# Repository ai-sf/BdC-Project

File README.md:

# Botta di Coulomb (BdC)

Quiz scientifico interattivo con scopi divulgativi, creato dall'Associazione Italiana Studenti di Fisica, Comitato Locale di Pavia. Realizzato in occasione della Notte Europea dei Ricercatori 2017 e riproposto in numerose altre occasioni.

Multi-player quiz game, designed for popularization activities: first developed for the European Researchers' Night 2017 by [AISF](http://ai-sf.it/) Pavia, and proposed in several other public or private events.

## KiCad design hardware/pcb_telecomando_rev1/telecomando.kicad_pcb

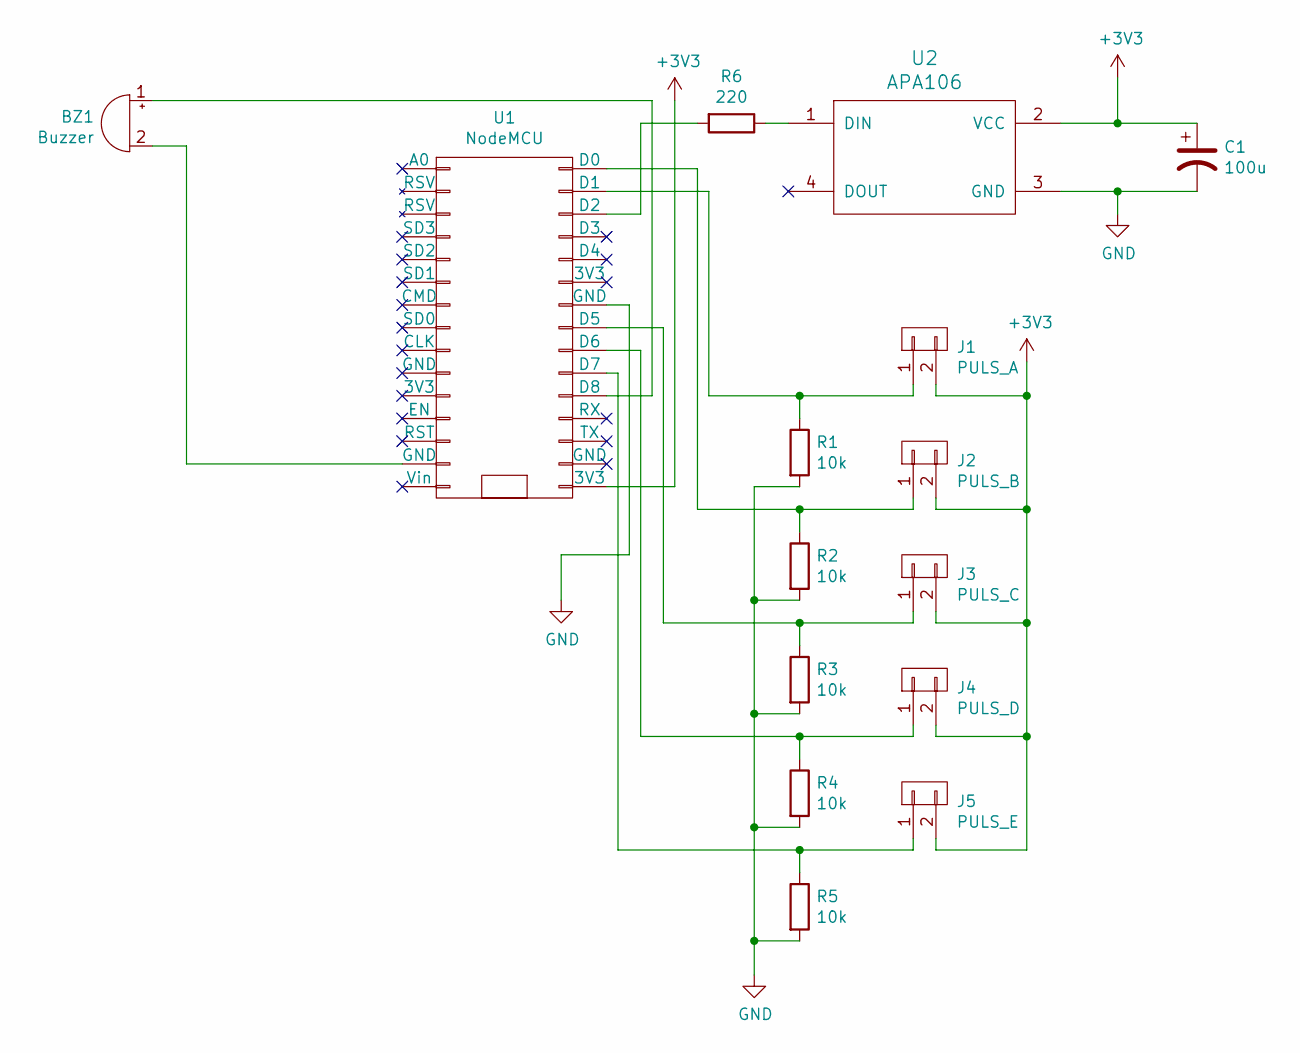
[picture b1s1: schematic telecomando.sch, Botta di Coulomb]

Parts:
BZ1: Buzzer; Buzzer_12x9.5RM7.6
C1: 100u; CP_Radial_D8.0mm_P2.50mm
J1: PULS_A; SW_PUSH-12mm
J2: PULS_B; SW_PUSH-12mm
J3: PULS_C; SW_PUSH-12mm
J4: PULS_D; SW_PUSH-12mm
J5: PULS_E; SW_PUSH-12mm
R1, R2, R3, R4, R5: 10k; Resistor_Horizontal_RM10mm
R6: 220; Resistor_Horizontal_RM10mm
U1: NodeMCU; NodeMCU_0.9
U2: APA106

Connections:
+3V3: C1.1, J1.2, J2.2, J3.2, J4.2, J5.2, U1.16 (3V3), U2.2 (VCC)
GND: C1.2, R1.2, R2.2, R3.2, R4.2, R5.2, U1.24 (GND), U2.3 (GND)
unnamed: BZ1.1 (-), U1.20 (D8)
unnamed: BZ1.2 (+), U1.14 (GND)
unnamed: J1.1, R1.1, U1.29 (D1)
unnamed: J2.1, R2.1, U1.30 (D0)
unnamed: J3.1, R3.1, U1.23 (D5)
unnamed: J4.1, R4.1, U1.22 (D6)
unnamed: J5.1, R5.1, U1.21 (D7)
unnamed: R6.1, U2.1 (DIN)
unnamed: R6.2, U1.28 (D2)

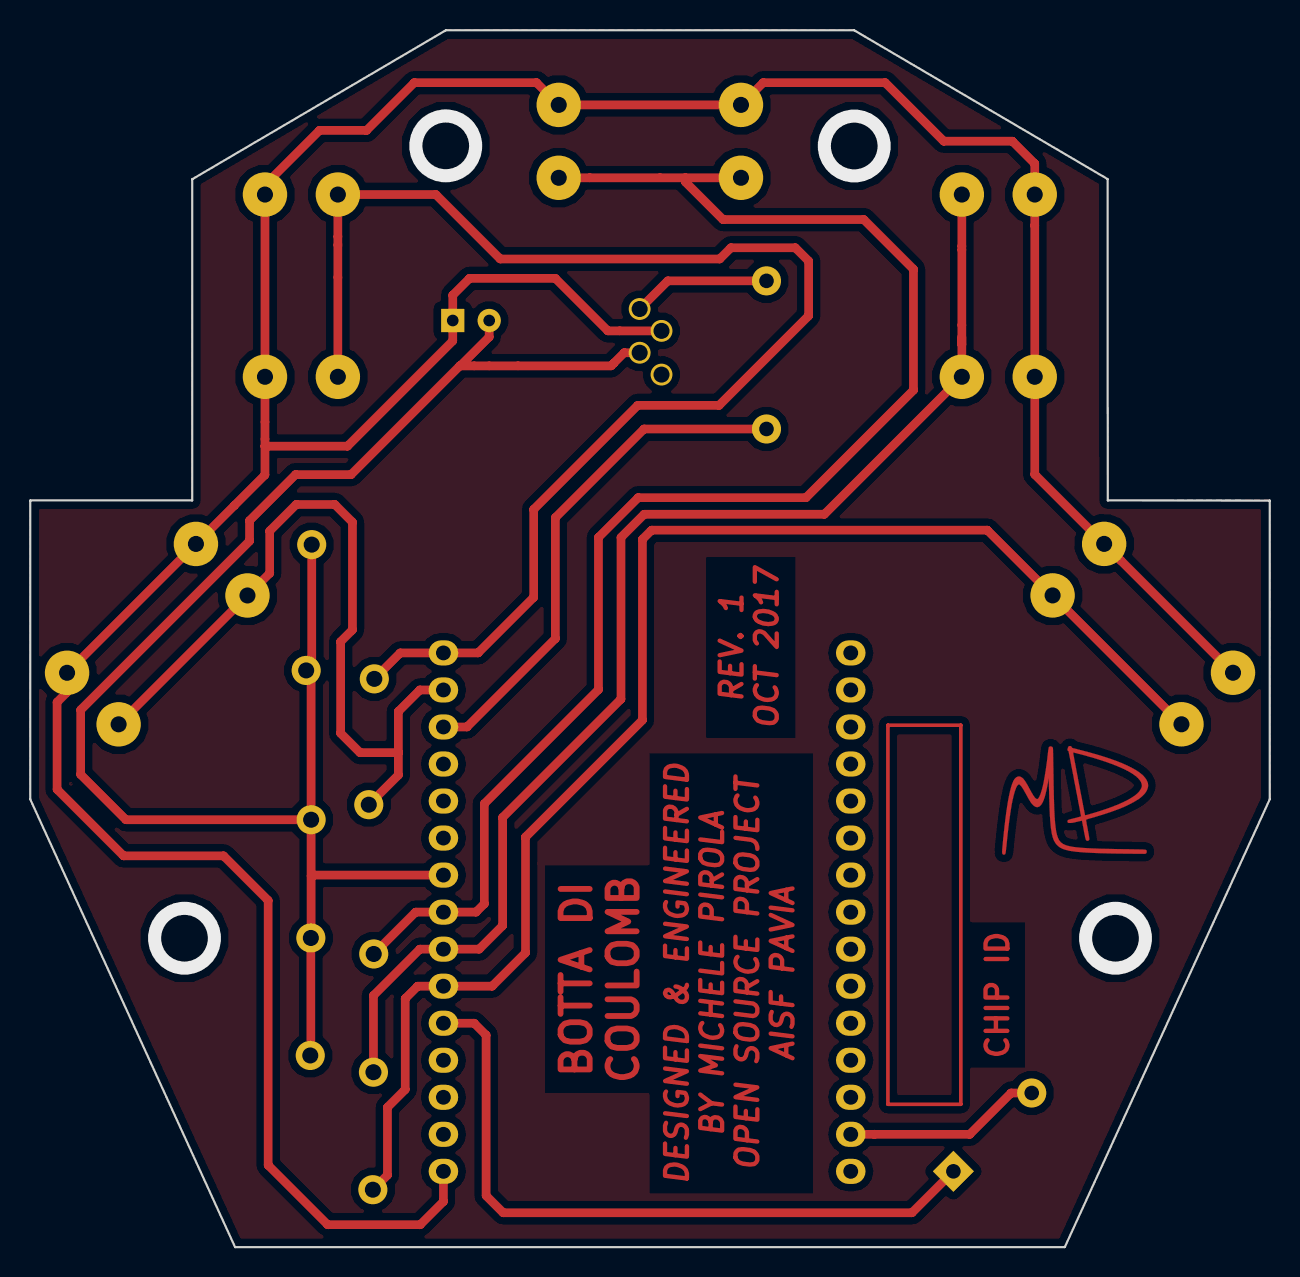
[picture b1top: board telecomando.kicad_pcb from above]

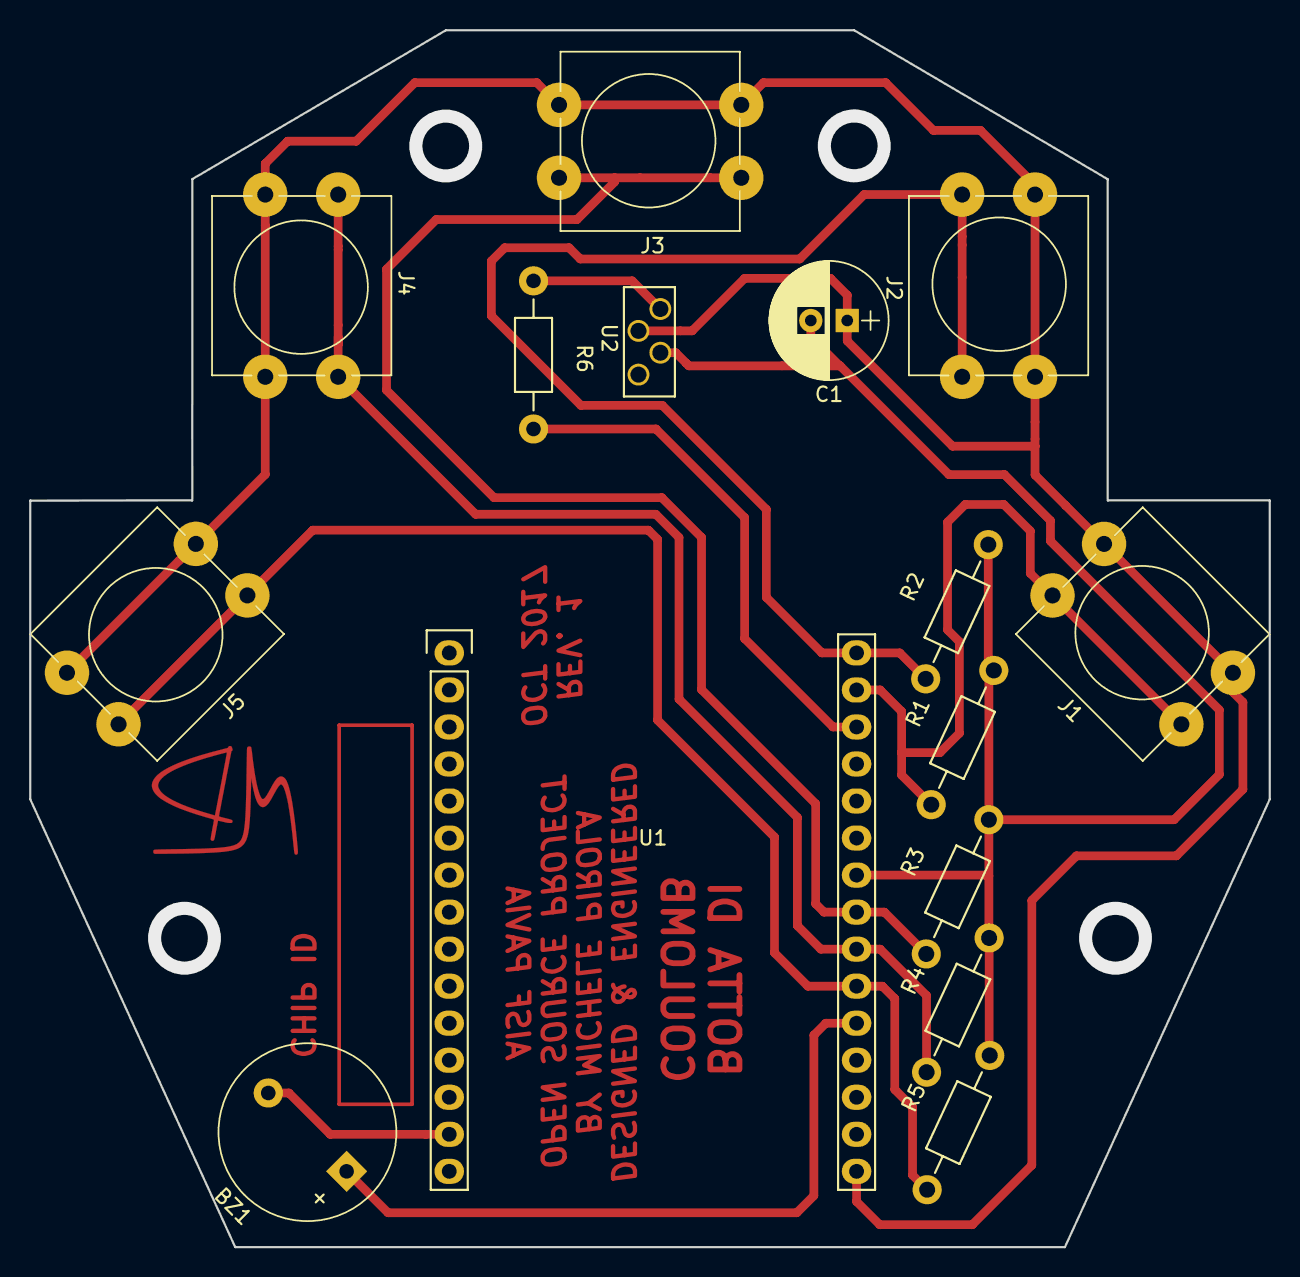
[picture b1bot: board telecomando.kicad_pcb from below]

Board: 2 copper layers, 85.0 x 83.5 mm, 15 parts (15 on the bottom side), 11 nets.

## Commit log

2018-09-06 add README
2018-09-06 added src
2018-09-06 credits and license
2018-09-06 added parameter file
2018-09-06 immagini
2018-09-06 modified main and questions
2018-09-06 added logoBdC_bianco.png
2018-09-06 moved port_name
2018-09-06 no serial mode
2018-09-06 prova_schermate
2018-09-06 removed backup
2018-09-06 CREDITS
2018-09-06 Ciao
2018-09-06 default comment
2018-09-06 fixed bugs
2018-09-07 deafult comment
2018-09-24 bdc v2.0
2018-09-24 removed MIG
2018-10-20 messo un poco a posto
2018-10-25 Update src/main.py, parameter_TEST.dat, src/utils/user.py files
2018-10-25 Update src/uix/firstslides.py, src/uix/scoregenbegin.py files
2018-10-29 Update src/uix/beforeqstslides.py, src/utils/user.py, src/uix/question.py, src/uix/scoregenscreen.py, src/uix/scoregenbegin.py files
2018-11-02 Update src/uix/scoregenscreen.py, src/uix/beforeqstslides.py files
2018-11-02 Update src/uix/question.py, src/uix/scoregenbegin.py, src/uix/scoregenscreen.py files
2018-11-02 Update src/uix/scoregenbegin.py, src/uix/scoregenscreen.py, src/uix/scoregenfinscreen.py, src/uix/scoresctscreen.py, src/uix/scoreqstscreen.py files
2018-11-05 Update src/utils/calculate_score.py, src/uix/scoregenfinscreen.py, src/utils/user.py, src/uix/scoregenscreen.py, src/uix/beforeqstslides.py files
2018-11-06 classifiche a terminale
2018-11-06 risolto bug frecce nella classifica dopo sezione
2018-11-06 classifica a terminale anche per sezioni speciali
2018-11-06 miglioramento stato domande a terminale
2018-11-06 shell per comandi runtime, luminosità modificabile
2018-11-06 controllo NaN su brightness e help per shell
2018-11-06 migliorata leggibilità classifiche a terminale
2018-11-06 classifica iniziale a terminale dopo sezione prova
2018-11-06 astensioni in classifica generale a terminale
2018-11-08 classe shell implementata in file esterno
2018-11-08 implementati bonus/malus arbitrari da shell
2018-11-08 popup bonus/malus
2018-11-08 possibile bonus/malus nascosto
2018-11-08 cambiati tutti testi pulsanti con icone
2018-11-08 aggiunto timer risposta
2018-11-09 timer risposta attivabile/disattivabile da file di configurazione
2018-11-09 risolto stiramento immagine logo
2018-11-09 controller su ogni schermata, ancora molto buggato
2018-11-09 installazione sdl2
2018-11-09 correzione errore libpng
2018-11-09 migliorata grafica countdown
2018-11-09 corretto bug colore countdown
2018-11-09 suono timer adattivo, tempo risposta impostabile
2018-11-09 aggiunti stop() di sicurezza per audio timer
2018-11-09 aggiunti file audio timer prima mancanti
2018-11-12 risolto bug audio timer che non si ferma
2018-11-12 tolto loop timer anche nel main (bug no stop())
2018-11-12 aggiunta risposta a classifica domanda a terminale
2018-11-12 aggiunto tempo a classifica domanda a terminale
2018-11-13 pulsante class. domanda per mostrare risposte date
2018-11-20 supporto lettura batteria telecomandi
2018-11-22 popup risposta premendo immagine in class. domanda
2018-11-22 cambiate lettere pulsanti con lettere cerchiate
2018-11-22 risolto bug carattere sbagliato popup astensione
2018-11-22 risolto bug risposte lunghe in popup
2018-11-24 risolto crash class. domanda dopo 5 astensioni
2018-11-26 aggiunto supporto UTF-8 (SCHRÖDINGER)
2018-11-26 modifiche comportamento finestra
2018-11-26 modifiche grafiche alla shell interna
2018-11-26 posizione in classif., migliorata grafica classif.
2018-11-27 no crash backup, ma domanda ripartenza è sbagliata
2018-11-28 risolto bug num. domanda e sez. ripetuta se backup
2018-11-28 sostituita unità di misura '"' con 's'
2018-11-28 ottimizzazione e pulizia del codice
2018-11-28 cambiato NOCONTROLLER in no_serial per coerenza fw
2018-11-28 miglioramento grafico separatore classifica
2019-01-04 migliore leggibilità classifica se tanti giocatori
2019-01-04 bande colorate e migliore disposizione testo punti
2019-01-04 correzione se 2 parole nel cognome (von Neumann)
2019-01-04 corretto nome file von Neumann
2019-01-04 aggiunte tutte le immagini dei fisici
2019-01-10 spazi classifiche terminale nomi lunghi/corti
2019-01-10 spostato bonus sezione con punti anziché con nome
2019-01-11 risposta giusta con colore diverso da pulsanti
2019-01-24 aggiornati codici telecomandi
2019-01-25 removed unused files and pycache files; added some credits and modified license
2019-01-25 reduced image size
2019-01-25 removed/moved some images (and fixed a source file accordingly); updated CREDITS
2019-01-31 commentato file parameter e ordinata la cartella di prova
2019-02-02 Update main.py (added link to pydelhi_mobile repository)
2019-02-02 updated README + CREDITS; replaced some images of physicists; fixed png; added a gitignore
2019-02-06 modificato codice telecomando Curie
2019-02-06 removed debug console messages + tested installation with virtualenv + updated README
2019-02-11 compatibilità telecomandi nuovi a 9 cifre
2019-02-18 img ricavata da cognome, codici non più duplicati
2019-02-19 cambiato colore risposta giusta
2019-02-22 aggiunto file domande prova telecomandi
2019-02-22 risolto crash classifica generale dopo backup
2019-02-22 backup non ripete ultima domanda, ancora problemi da risolvere in casi particolari (fine sezione o ultima domanda)
2019-02-28 risolti bug backup e aggiornamento backup alla visualizzazione risposta esatta
2019-03-01 corretto bug posizione classifica se doppia parità
2019-03-04 modifiche per coerenza con file configurazione
2019-03-05 eliminato fullscreen inutilizzato, razionalizzato file parametri
2019-03-08 corretto crash se accenti in finestra risposta
2019-03-16 visualizzazione topologia mesh a terminale
2019-03-18 riconosciuto controller in topologia
2019-04-08 tempo risposta impostabile per ogni sezione
2019-04-09 corretti bug tasto classifica disabilitato
2019-04-09 scelta num. domande finali e classifica in sezione
2019-04-10 razionalizzazione file di configurazione
2019-04-11 tempo risposta nullo per prova domande veloce
2019-04-11 suono e colore timer riferiti solo ultimo minuto
2019-10-06 new README + new test_game
2019-10-07 aggiunti HW + FW + meccanica e fatto ordine
2019-10-07 spostato software nella sua cartella
2019-10-08 Add LICENSE
2023-11-11 committ test
2023-11-11 First step towards python3, it works!
2023-11-14 Tutti i print resi in python3 fino all'avio del gioco
2023-11-14 Uso per Windows
2023-11-14 Revert "Tutti i print resi in python3 fino all'avio del gioco, perchè ho sbagliato branch"
    This reverts commit d6568281c91b2fcb9fad0d82c62ddc50f7d323d4.
2023-11-14 Fix dei flöoat to int
2023-11-14 Fixed the view of test's questions
2023-11-14 should fix font errot
2023-11-14 fixes Grid ID problems
2023-11-14 Fixing most float to int conversion
2023-11-14 fixes Rawdic.iteritems
2023-11-14 lighter fix for float to int
2023-11-14 Solo un po di cambiamenti test_game.dat
2023-11-14 test Linux compatibility and added requirments.txt
2023-11-15 aggiustato distorsione immagini in classifica domanda
2023-12-11 Uniformazione di tutte le classifiche, in modo che tutti i nomi siano dello stesso colore
2023-12-12 piccola miglioria gestione errore connessione porta seriale
2023-12-13 avevo dimenticato print del debug
2023-12-14 Modifiche per testare il gico con i telecomandi senza avere i telecomandi
2023-12-19 chiudere finestra con esc
2024-03-25 ora si è capito cosa stava a fare 10^-6
2024-03-25 piccolo vademecum per capire cosa cambiare tra master ed emulatore in caso si vogliano fare dei test
2024-03-26 documentation
2024-04-15 aggiustato calcolo dei tempi per astensioni
2024-12-05 punti bonus ora funzionano
2024-12-06 tolti print debug
2024-12-07 aggiustata la shell con autocompletamento per attribuzione punti bonus
